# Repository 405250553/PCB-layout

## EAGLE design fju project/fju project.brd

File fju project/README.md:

# FJU 大三專題 layout

## PCB layout 正面
<p align="left">

</p>

## PCB layout 背面
<p align="left">

</p>

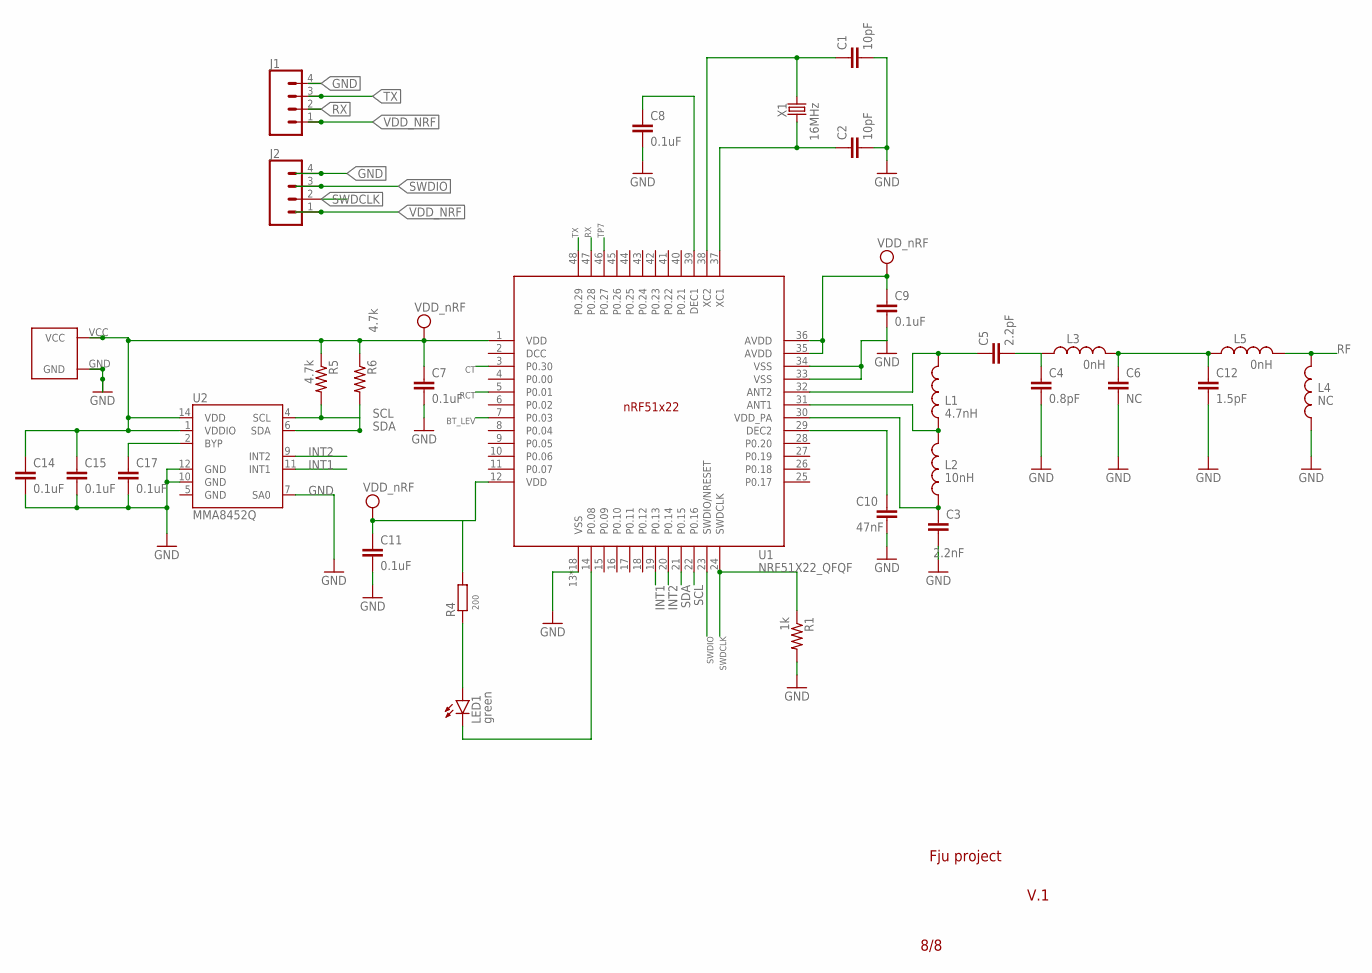
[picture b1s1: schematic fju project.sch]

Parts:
C1, C2: 10pF; RESC0402_N
C3: 2.2nF; RESC0402_N
C4: 0.8pF; RESC0402_N
C5: 2.2pF; RESC0402_N
C6: NC; RESC0402_N
C7, C8, C9, C11, C14, C15, C17: 0.1uF; RESC0402_N
C10: 47nF; RESC0402_N
C12: 1.5pF; RESC0402_N
J1, J2: CONN_04; 1X04
L1: 4.7nH; RESC0402_N; MPN CE201210-4N7J.
L2: 10nH; RESC0402_N
L3, L5: 0nH; RESC0402_N
L4: NC; RESC0402_N
LED1: green; SML0603
R1: 1k; R0402
R4: 200; RESC0402_N
R5, R6: 4.7k; R0402
U1: NRF51X22_QFQF; QFN40P600X600X90-48_N
U2: MMA8452Q; QFN-16_0.5MM
U$1: CR2032; CR2032-20MM
X1: 16MHz; 2.5X2.0_KX-6

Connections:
BT_LEV: U1.7 (P0.03)
BYP: C17.1, U2.2 (BYP)
CT: U1.3 (P0.30)
DCC: U1.2 (DCC)
GND: C1.2, C2.2, C3.2, C4.2, C6.2, C7.2, C8.2, C9.2, C10.2, C11.2, C12.2, C14.2, C15.2, C17.2, J1.4, J2.4, L4.1, R1.2, U1.13 (VSS), U1.33 (VSS), U1.34 (VSS), U1.PAD (VSS), U1.PAD@VIA01 (VSS), U1.PAD@VIA02 (VSS), U1.PAD@VIA03 (VSS), U1.PAD@VIA04 (VSS), U1.PAD@VIA05 (VSS), U1.PAD@VIA06 (VSS), U1.PAD@VIA07 (VSS), U1.PAD@VIA08 (VSS), U1.PAD@VIA09 (VSS), U1.PAD@VIA10 (VSS), U1.PAD@VIA11 (VSS), U1.PAD@VIA12 (VSS), U1.PAD@VIA13 (VSS), U1.PAD@VIA14 (VSS), U1.PAD@VIA15 (VSS), U1.PAD@VIA16 (VSS), U2.7 (SA0), U2.10 (GND), U2.12 (GND), U$1.GND
INT1: U1.19 (P0.13), U2.11 (INT1)
INT2: U1.20 (P0.14), U2.9 (INT2)
unnamed: L1.1, L2.2, U1.31 (ANT1)
unnamed: LED1.A, R4.1
unnamed: C1.1, U1.38 (XC2), X1.1
unnamed: C4.1, C5.2, L3.1
unnamed: C10.1, U1.29 (DEC2)
unnamed: C8.1, U1.39 (DEC1)
unnamed: C3.1, L2.1, U1.30 (VDD_PA)
unnamed: C5.1, L1.2, U1.32 (ANT2)
unnamed: C6.1, C12.1, L3.2, L5.1
P0.08: LED1.C, U1.14 (P0.08)
P0.18: U1.46 (P0.27)
RCT: U1.5 (P0.01)
RF: L4.2, L5.2
RX: J1.2, U1.47 (P0.28)
SCL: R5.2, U1.22 (P0.16), U2.4 (SCL)
SDA: R6.2, U1.21 (P0.15), U2.6 (SDA)
SWDCLK: J2.2, R1.1, U1.24 (SWDCLK)
SWDIO: J2.3, U1.23 (SWDIO/NRESET)
TX: J1.3, U1.48 (P0.29)
VDD_NRF: C7.1, C9.1, C11.1, C14.1, C15.1, J1.1, J2.1, R4.2, R5.1, R6.1, U1.1 (VDD), U1.12 (VDD), U1.35 (AVDD), U1.36 (AVDD), U2.1 (VDDIO), U2.14 (VDD), U$1.VCC
X1: C2.1, U1.37 (XC1), X1.3 (2)

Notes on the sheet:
Fju project
V.1
8/8

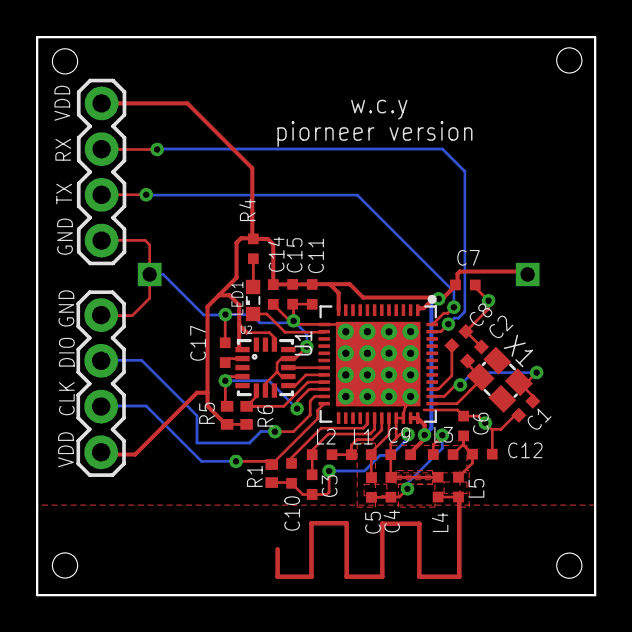
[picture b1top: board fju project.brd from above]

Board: 2 copper layers, 31.0 x 31.0 mm, 31 parts (1 on the bottom side), 23 nets.

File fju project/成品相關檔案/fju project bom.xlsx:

Qty | Value | Device | Package | Parts | REFERENCE
1 | 4.7uF | CAPACITOR_0402_N | RESC0402_N | C7 | X5R,20%
6 | 0.1uF | CAPACITOR_0402_N | RESC0402_N | C8, C9, C11, C14, C15, C17 | X7R ±10% 10V
1 | 0.8pF | CAPACITOR_0402_N | RESC0402_N | C4 | NPO ± 0.1PF 50V
2 | 0nH | INDUCTOR_0402_N | RESC0402_N | L3, L5
1 | 1.5pF | CAPACITOR_0402_N | RESC0402_N | C12 | NPO ± 0.25PF 50V
1 | 10nH | INDUCTOR_0402_N | RESC0402_N | L2 | ±5%
2 | 10pF | CAPACITOR_0402_N | RESC0402_N | C1, C2 | NPO ± 5% 50V
1 | 16MHz | KX-6 | 2.5X2.0_KX-6 | X1 | ±10 ppm
1 | 1k | R-US_R0402 | R0402 | R1
1 | 2.2nF | CAPACITOR_0402_N | RESC0402_N | C3 | X7R ±10% 50V
1 | 2.2pF | CAPACITOR_0402_N | RESC0402_N | C5 | NPO ± 0.25PF 50V
1 | 200 | RESISTOR_0402_N | RESC0402_N | R4
2 | 4.7k | R-US_R0402 | R0402 | R5, R6 | ±5%
1 | 4.7nH | INDUCTOR_0402_N | RESC0402_N | L1 | ±0.3%
1 | 47nF | CAPACITOR_0402_N | RESC0402_N | C10 | X7R ±10% 16V
1 | MMA8452Q | MMA8452Q | QFN-16_0.5MM | U2
1 | NRF51X22_QFQF | NRF51X22_QFQF | QFN40P600X600X90-48_N | U1
1 | green | LEDSML0603 | SML0603 | LED1

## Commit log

2019-10-30 update.2019/10/30

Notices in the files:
parts and their libraries:
crystal-geyer_V1_0: Copyright: Geyer-Electronic
SparkFun-Connectors: Licensing: Creative Commons ShareAlike 4.0 International - https://creativecommons.org/licenses/by-sa/4.0
